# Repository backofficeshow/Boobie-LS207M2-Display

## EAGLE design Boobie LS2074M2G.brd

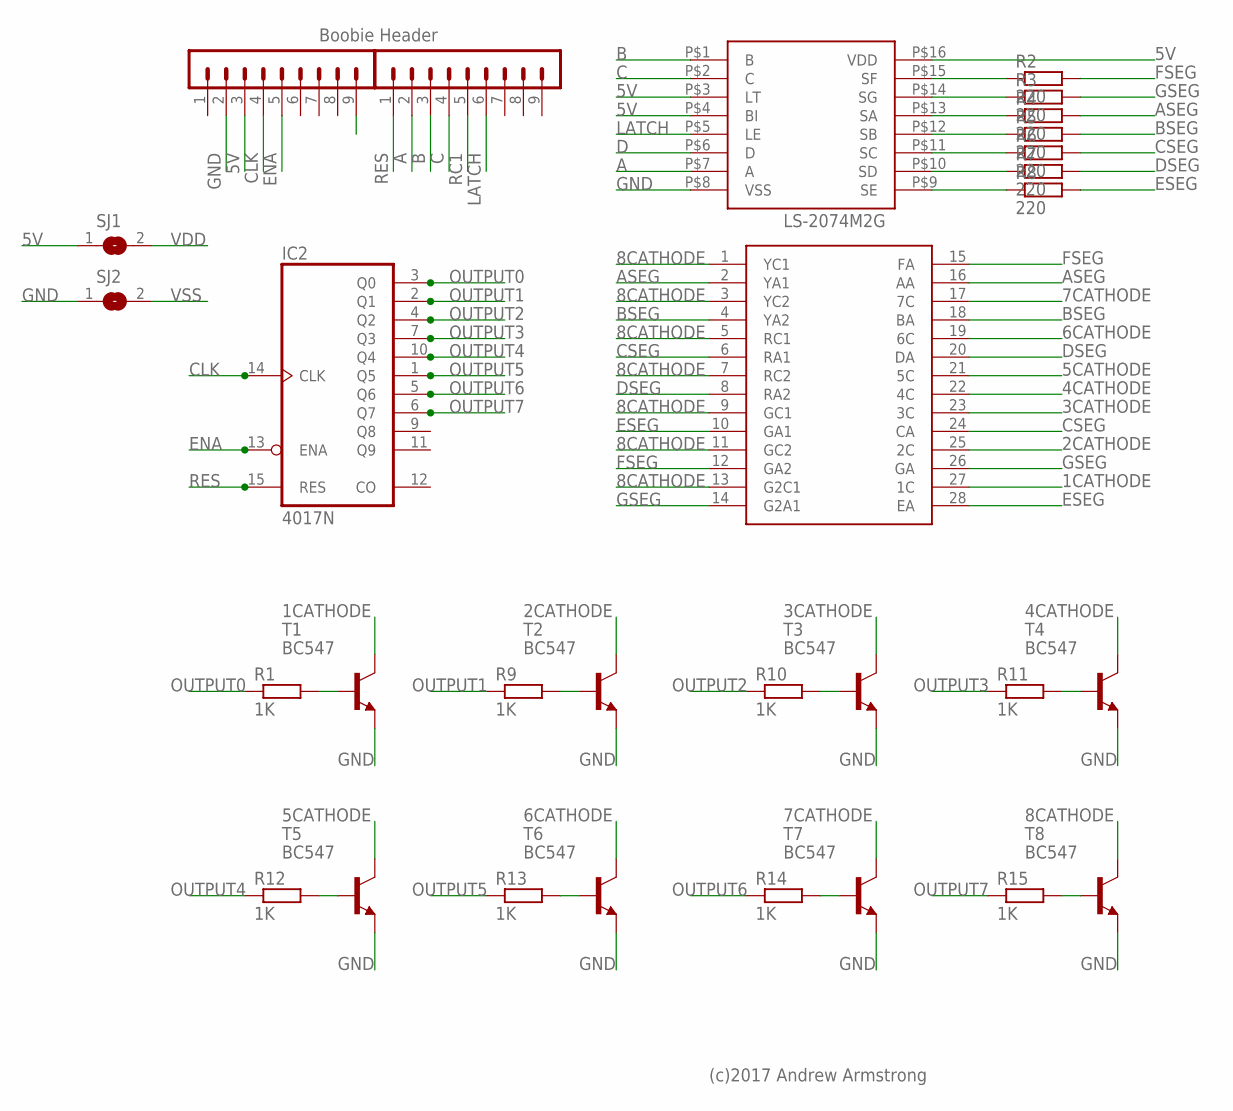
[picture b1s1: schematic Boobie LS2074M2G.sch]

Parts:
IC2: 4017N; DIL16
R1, R9, R10, R11, R12, R13, R14, R15: 1K; 0204/7
R2, R3, R4, R5, R6, R7, R8: 220; 0204/7
SJ1, SJ2: SJ
SV1, SV2: MA09-1
T1, T2, T3, T4, T5, T6, T7, T8: BC547; TO92
U$1: LS-2074M2G
U$2: MC14511B; DIL16

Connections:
1CATHODE: T1.3 (C), U$1.27 (1C)
2CATHODE: T2.3 (C), U$1.25 (2C)
3CATHODE: T3.3 (C), U$1.23 (3C)
4CATHODE: T4.3 (C), U$1.22 (4C)
5CATHODE: T5.3 (C), U$1.21 (5C)
5V: SJ1.1, SV2.3, U$2.P$3 (LT), U$2.P$4 (BI), U$2.P$16 (VDD)
6CATHODE: T6.3 (C), U$1.19 (6C)
7CATHODE: T7.3 (C), U$1.17 (7C)
8CATHODE: T8.3 (C), U$1.1 (YC1), U$1.3 (YC2), U$1.5 (RC1), U$1.7 (RC2), U$1.9 (GC1), U$1.11 (GC2), U$1.13 (G2C1)
A: SV1.2, U$2.P$7 (A)
ASEG: R4.2, U$1.2 (YA1), U$1.16 (AA)
B: SV1.3, U$2.P$1 (B)
BSEG: R5.2, U$1.4 (YA2), U$1.18 (BA)
C: SV1.4, U$2.P$2 (C)
CLK: IC2.14 (CLK), SV2.4
CSEG: R6.2, U$1.6 (RA1), U$1.24 (CA)
D: U$2.P$6 (D)
DSEG: R7.2, U$1.8 (RA2), U$1.20 (DA)
ENA: IC2.13 (ENA), SV2.5
ESEG: R8.2, U$1.10 (GA1), U$1.28 (EA)
FSEG: R2.2, U$1.12 (GA2), U$1.15 (FA)
GND: SJ2.1, SV2.2, T1.1 (E), T2.1 (E), T3.1 (E), T4.1 (E), T5.1 (E), T6.1 (E), T7.1 (E), T8.1 (E), U$2.P$8 (VSS)
GSEG: R3.2, U$1.14 (G2A1), U$1.26 (GA)
LATCH: SV1.6, U$2.P$5 (LE)
unnamed: R9.2, T2.2 (B)
unnamed: R10.2, T3.2 (B)
unnamed: R11.2, T4.2 (B)
unnamed: R12.2, T5.2 (B)
unnamed: R13.2, T6.2 (B)
unnamed: R14.2, T7.2 (B)
unnamed: R15.2, T8.2 (B)
unnamed: R1.2, T1.2 (B)
unnamed: R2.1, U$2.P$15 (SF)
unnamed: R3.1, U$2.P$14 (SG)
unnamed: R4.1, U$2.P$13 (SA)
unnamed: R5.1, U$2.P$12 (SB)
unnamed: R6.1, U$2.P$11 (SC)
unnamed: R7.1, U$2.P$10 (SD)
unnamed: R8.1, U$2.P$9 (SE)
OUTPUT0: IC2.3 (Q0), R1.1
OUTPUT1: IC2.2 (Q1), R9.1
OUTPUT2: IC2.4 (Q2), R10.1
OUTPUT3: IC2.7 (Q3), R11.1
OUTPUT4: IC2.10 (Q4), R12.1
OUTPUT5: IC2.1 (Q5), R13.1
OUTPUT6: IC2.5 (Q6), R14.1
OUTPUT7: IC2.6 (Q7), R15.1
RC1: SV1.5
RES: IC2.15 (RES), SV1.1
VDD: IC2.16 (VDD), SJ1.2
VSS: IC2.8 (VSS), SJ2.2

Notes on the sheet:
(c)2017 Andrew Armstrong
Boobie Header

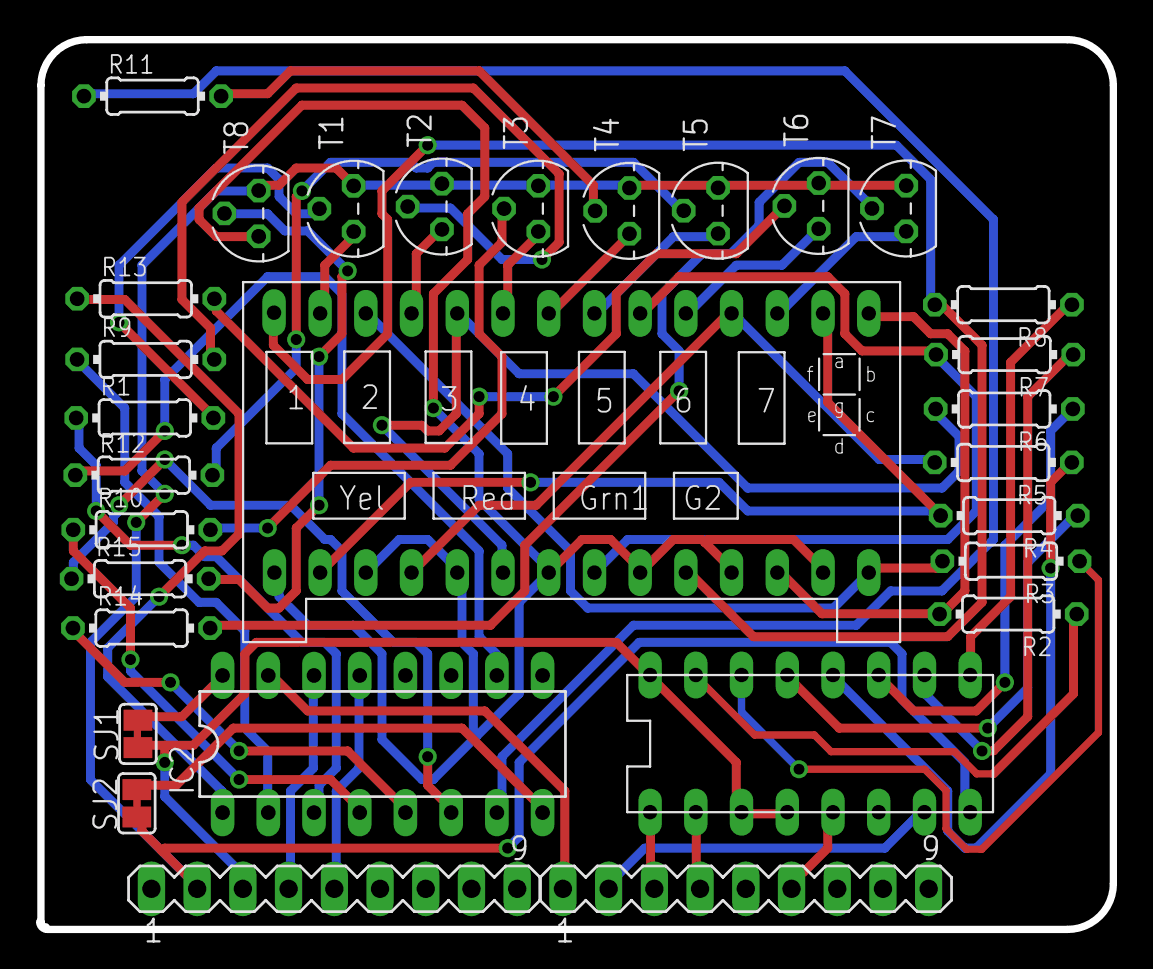
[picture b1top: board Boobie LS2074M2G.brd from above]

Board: 2 copper layers, 59.7 x 49.4 mm, 30 parts (0 on the bottom side), 49 nets.

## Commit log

2017-07-28 Initial Commit!
    Warning this design might not work! Totally untested as of now!
